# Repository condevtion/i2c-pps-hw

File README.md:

# Schematics for Programmable DC-DC Power Supply with I2C Interface

## About

The repository contains a schematic for the Programmable Power Supply.

## Specifications
- Controller: Texas Instruments [BQ25758S](https://www.ti.com/product/BQ25758S)
- Input voltage: 5V (4-6V - hardware power good window)
- Input current: up to 5A (hardware limited)
- Output voltage: programmable by I2C in controller defined range (3.3 - 26V)
- Output current: up to 5A (hardware limited)
- Switching frequency: 250kHz

## Schematics Structure
The device is complex enough for the schematics to be split into several pages, one for each functional block.
- Controller and Power Stage - consists of the BQ25758S controller, the power MOSFETs, and the inductor
- Input Filter and Sensor - a set of input capacitors and the input current sense resistor connected according to 4-point probes (Kelvin) method
- Output Filter and Sensor - the same for output circuit
- Master Switch - an input protection and an electronically controllable power switch
- Digital I/O and Indication - digital interface between controller and I2C host, contains as well a status LED, a power good LED, and an independent voltage regulator for the digital circuit
- Programming - a set of resistors to define controller's operating mode and HW limits for voltage and current
For now the pages contain mainly just network and hierarchical labels.

## Major Networks and Busses
- **`+5V_Prot`** - protected positive input voltage. The master switch page contains an input connector and protection circuit (fuse, TVS diode, polarity protection) after which the network starts. It is used as well to power the digital I/O and indication block
- **`VINP`** - positive input voltage after the master switch itself (goes to the input filter)
- **`EN`** - master switch control signal (should be high to turn the switch on and low to turn it OFF)
- **`VINN`** - output of the input filter
- **`VOUT`** - the output voltages bus (contains power stage output and whole device output networks, goes to the output filter)
- **`I2C`** - I2C bus itself (connected to `SCL` and `SDA` pins)
- **`GPIO`** - groups digital I/O lines: interrupt, power good, status, and chip enable
- **`PROG`** - groups the rest of analog input lines which should be connected to the programming block to set operating mode and limits for the controller

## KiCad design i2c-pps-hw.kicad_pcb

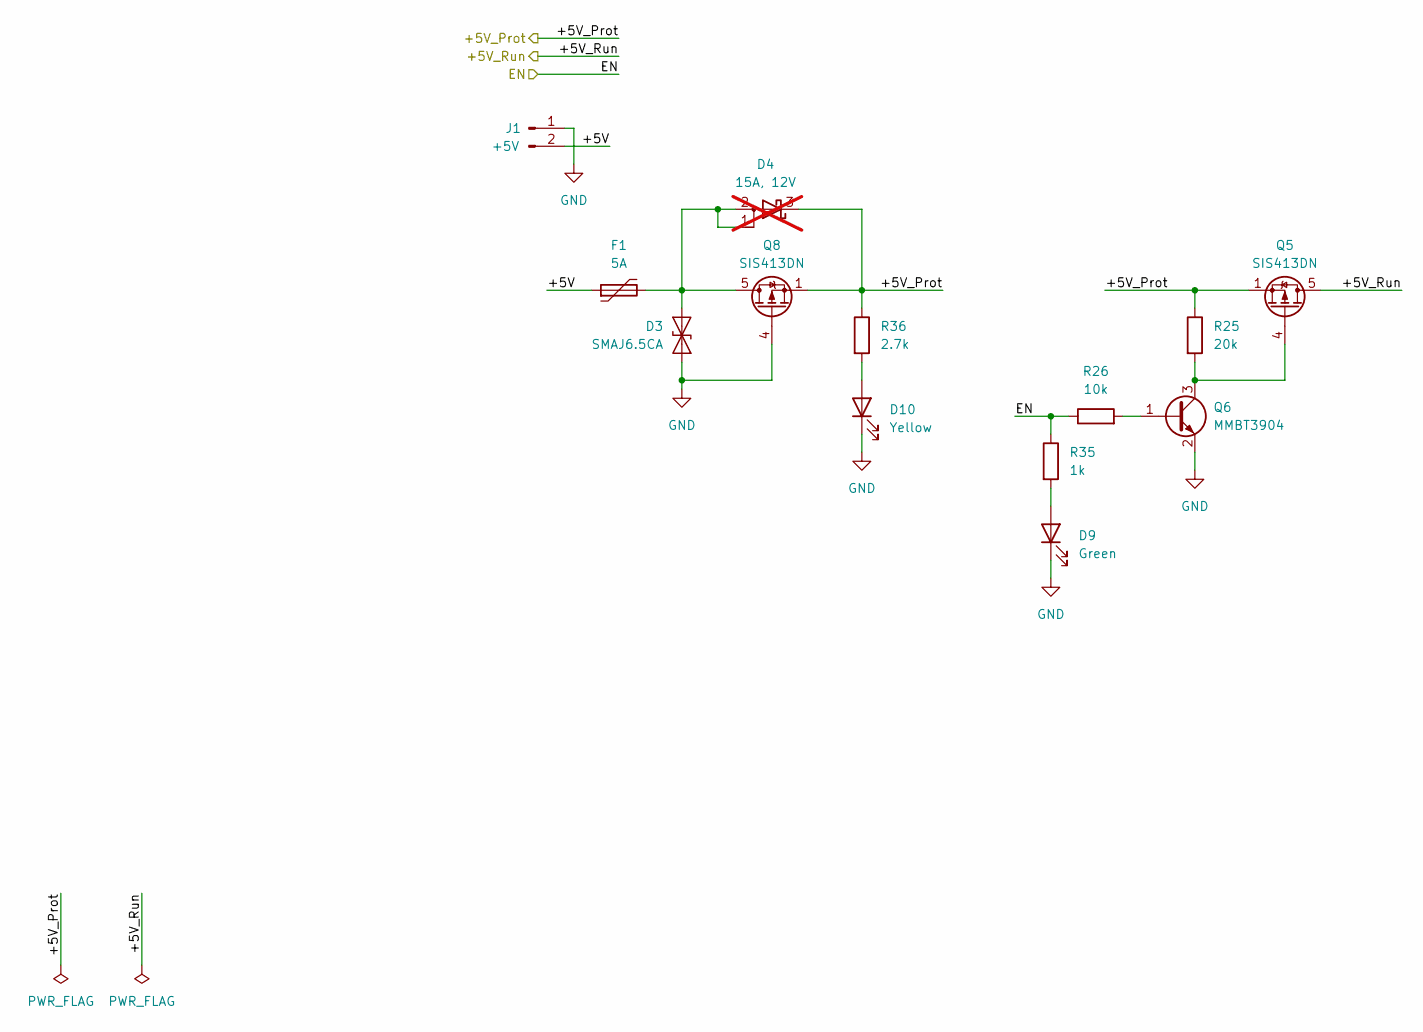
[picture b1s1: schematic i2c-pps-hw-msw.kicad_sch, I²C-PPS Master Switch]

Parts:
D3: SMAJ6.5CA; D_SMA; Part Number SMAJ6.5CA-AT/TR13
D4: 15A, 12V; TO-277A_ThermalVias; Part Number FSV15100V; not fitted
D9: Green; LED_0603_1608Metric_Pad1.05x0.95mm_HandSolder; Part Number LTST-C190GKT
D10: Yellow; LED_0603_1608Metric_Pad1.05x0.95mm_HandSolder; Part Number LTST-C190YKT
F1: 5A; Fuse_2920_7451Metric; Part Number SMD2920B500TF
J1: +5V; TE_1-1123724-2; Part Number 1-1123724-2
Q5, Q8: SIS413DN; Vishay_PowerPAK_1212-8_Single_ThermalVias; Part Number SIS413DN-T1-GE3
Q6: MMBT3904; SOT-23; Part Number MMBT3904-TP
R25: 20k; R_0603_1608Metric_Pad0.98x0.95mm_HandSolder; Part Number RC0603JR-0720KL
R26: 10k; R_0603_1608Metric_Pad0.98x0.95mm_HandSolder; Part Number RC0603JR-0710KL
R35: 1k; R_0603_1608Metric_Pad0.98x0.95mm_HandSolder; Part Number RC0603JR-071KL
R36: 2.7k; R_0603_1608Metric_Pad0.98x0.95mm_HandSolder; Part Number RC0603JR-072K7L

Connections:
/Controller and Power Stage/+5V_Run: Q5.5 (D); also elsewhere on the board
/Digital IO and Indication/+5V_Prot: D4.3 (K), Q5.1 (S), Q5.2 (S), Q5.3 (S), Q8.1 (S), Q8.2 (S), Q8.3 (S), R25.1, R36.1; also elsewhere on the board
/Digital IO and Indication/EN: R26.1, R35.1; also elsewhere on the board
/Master Switch/+5V: F1.1, J1.2
GND: D3.1 (A1), D9.1 (K), D10.1 (K), J1.1, Q6.2 (E), Q8.4 (G); also elsewhere on the board
unnamed: D3.2 (A2), D4.1 (A), D4.2 (A), F1.2, Q8.5 (D)
unnamed: D9.2 (A), R35.2
unnamed: D10.2 (A), R36.2
unnamed: Q5.4 (G), Q6.3 (C), R25.2
unnamed: Q6.1 (B), R26.2

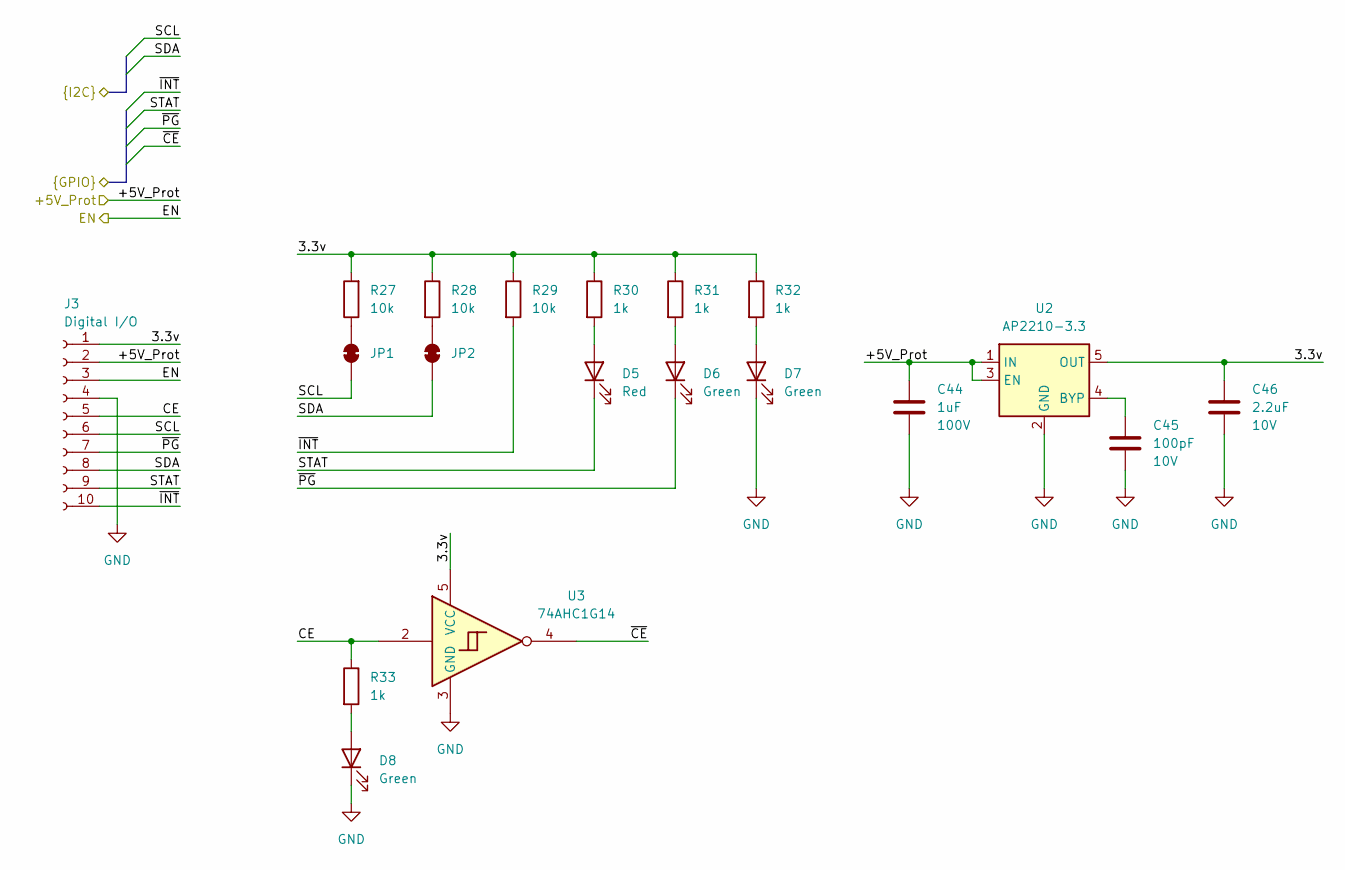
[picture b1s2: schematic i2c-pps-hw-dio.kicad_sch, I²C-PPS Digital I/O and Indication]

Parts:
C44: 1uF; C_0805_2012Metric; Rated Voltage 100V; Part Number 08051C105K4Z2A
C45: 100pF; C_0603_1608Metric_Pad1.08x0.95mm_HandSolder; Rated Voltage 10V; Part Number 885012206003
C46: 2.2uF; C_0603_1608Metric_Pad1.08x0.95mm_HandSolder; Rated Voltage 10V; Part Number GRM188R71A225KE15J
D5: Red; LED_0603_1608Metric_Pad1.05x0.95mm_HandSolder; Part Number LTST-C193KRKT-2A
D6, D7, D8: Green; LED_0603_1608Metric_Pad1.05x0.95mm_HandSolder; Part Number LTST-C190GKT
J3: Digital I/O; PinSocket_2x05_P2.54mm_Vertical; Part Number PPPC052LFBN-RC
JP1, JP2: SolderJumper-2_P0.65mm_Bridged_RoundedPad0.5x0.75mm
R27, R28, R29: 10k; R_0603_1608Metric_Pad0.98x0.95mm_HandSolder; Part Number RC0603JR-0710KL
R30, R31, R32, R33: 1k; R_0603_1608Metric_Pad0.98x0.95mm_HandSolder; Part Number RC0603JR-071KL
U2: AP2210-3.3; SOT-23-5; Part Number AP2210N-3.3TRG1
U3: 74AHC1G14; SOT-23-5_HandSoldering; Part Number SN74AHC1G14DBVR

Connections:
/Controller and Power Stage/SCL: J3.6, JP1.1 (A); also elsewhere on the board
/Controller and Power Stage/SDA: J3.8, JP2.1 (A); also elsewhere on the board
/Controller and Power Stage/STAT: D5.1 (K), J3.9; also elsewhere on the board
/Controller and Power Stage/~CE: U3.4; also elsewhere on the board
/Controller and Power Stage/~INT: J3.10, R29.2; also elsewhere on the board
/Controller and Power Stage/~PG: D6.1 (K), J3.7; also elsewhere on the board
/Digital IO and Indication/3.3v: C46.1, J3.1, R27.2, R28.1, R29.1, R30.1, R31.1, R32.1, U2.5 (OUT), U3.5 (VCC)
/Digital IO and Indication/+5V_Prot: C44.1, J3.2, U2.1 (IN), U2.3 (EN); also elsewhere on the board
/Digital IO and Indication/CE: J3.5, R33.1, U3.2
/Digital IO and Indication/EN: J3.3; also elsewhere on the board
GND: C44.2, C45.2, C46.2, D7.1 (K), D8.1 (K), J3.4, U2.2 (GND), U3.3 (GND); also elsewhere on the board
unnamed: D5.2 (A), R30.2
unnamed: D6.2 (A), R31.2
unnamed: D7.2 (A), R32.2
unnamed: D8.2 (A), R33.2
unnamed: JP1.2 (B), R27.1
unnamed: JP2.2 (B), R28.2
unnamed: C45.1, U2.4 (BYP)

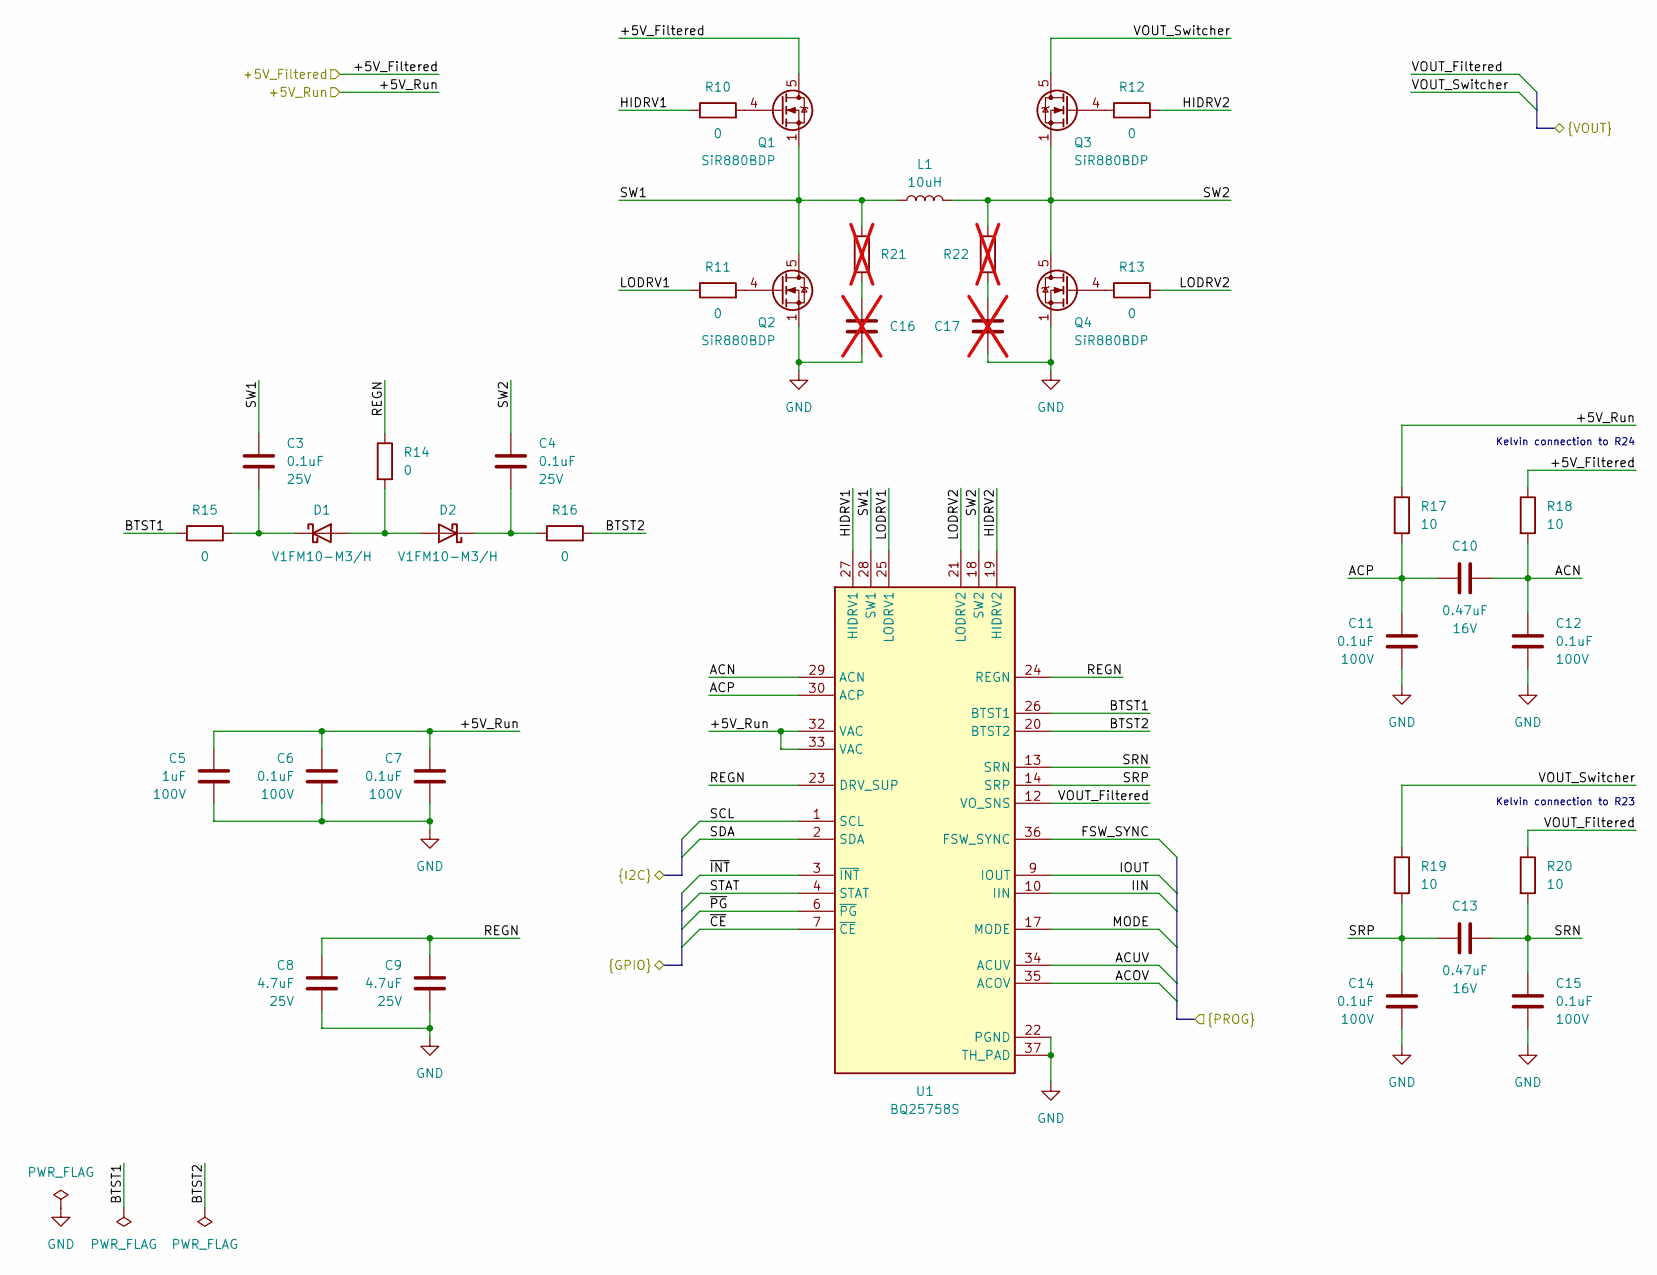
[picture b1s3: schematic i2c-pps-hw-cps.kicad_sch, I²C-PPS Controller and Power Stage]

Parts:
C3, C4: 0.1uF; C_0603_1608Metric_Pad1.08x0.95mm_HandSolder; Rated Voltage 25V; Part Number C0603C104K3RACTU
C5: 1uF; C_0805_2012Metric; Rated Voltage 100V; Part Number 08051C105K4Z2A
C6, C7, C11, C12, C14, C15: 0.1uF; C_0603_1608Metric_Pad1.08x0.95mm_HandSolder; Rated Voltage 100V; Part Number HMK107B7104KAHT
C8, C9: 4.7uF; C_0805_2012Metric; Rated Voltage 25V; Part Number CGA4J1X7R1E475K125AE
C10, C13: 0.47uF; C_0603_1608Metric_Pad1.08x0.95mm_HandSolder; Rated Voltage 16V; Part Number CL10B474KO8NNNC
C16, C17: C_0805_2012Metric; not fitted
D1, D2: V1FM10-M3/H; D_SMF; Part Number V1FM10-M3/H
L1: 10uH; L_Bourns_SRP1038A_10.0x11.0mm; Part Number SRP1038A-100M
Q1, Q2, Q3, Q4: SiR880BDP; PowerPAK_SO-8_Single_ThermalVias; Part Number SIR880BDP-T1-RE3
R10, R11, R12, R13, R15, R16: 0; R_0603_1608Metric_Pad0.98x0.95mm_HandSolder; Part Number RC0603JR-070RL
R14: 0; R_0805_2012Metric; Part Number CRCW08050000Z0EAC
R17, R18, R19, R20: 10; R_0603_1608Metric_Pad0.98x0.95mm_HandSolder; Part Number RC0603FR-0710RL
R21, R22: R_1210_3225Metric; not fitted
U1: BQ25758S; Texas_RRV0036A_VQFN-36-1EP_4.8x5.8mm_P0.5mm_EP3.6x4.6mm_The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; Part Number BQ25758SRRVR

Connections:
/Controller and Power Stage/+5V_Filtered: Q1.5 (D), R18.1; also elsewhere on the board
/Controller and Power Stage/+5V_Run: C5.1, C6.1, C7.1, R17.1, U1.32 (VAC), U1.33 (VAC); also elsewhere on the board
/Controller and Power Stage/ACN: C10.1, C12.1, R18.2, U1.29 (ACN)
/Controller and Power Stage/ACOV: U1.35 (ACOV); also elsewhere on the board
/Controller and Power Stage/ACP: C10.2, C11.1, R17.2, U1.30 (ACP)
/Controller and Power Stage/ACUV: U1.34 (ACUV); also elsewhere on the board
/Controller and Power Stage/BTST1: R15.1, U1.26 (BTST1)
/Controller and Power Stage/BTST2: R16.2, U1.20 (BTST2)
/Controller and Power Stage/FSW_SYNC: U1.36 (FSW_SYNC); also elsewhere on the board
/Controller and Power Stage/HIDRV1: R10.1, U1.27 (HIDRV1)
/Controller and Power Stage/HIDRV2: R12.2, U1.19 (HIDRV2)
/Controller and Power Stage/IIN: U1.10 (IIN); also elsewhere on the board
/Controller and Power Stage/IOUT: U1.9 (IOUT); also elsewhere on the board
/Controller and Power Stage/LODRV1: R11.1, U1.25 (LODRV1)
/Controller and Power Stage/LODRV2: R13.2, U1.21 (LODRV2)
/Controller and Power Stage/MODE: U1.17 (MODE); also elsewhere on the board
/Controller and Power Stage/REGN: C8.1, C9.1, R14.1, U1.23 (DRV_SUP), U1.24 (REGN)
/Controller and Power Stage/SCL: U1.1 (SCL); also elsewhere on the board
/Controller and Power Stage/SDA: U1.2 (SDA); also elsewhere on the board
/Controller and Power Stage/SRN: C13.1, C15.1, R20.2, U1.13 (SRN)
/Controller and Power Stage/SRP: C13.2, C14.1, R19.2, U1.14 (SRP)
/Controller and Power Stage/STAT: U1.4 (STAT); also elsewhere on the board
/Controller and Power Stage/SW1: C3.1, L1.1, Q1.1 (S), Q1.2 (S), Q1.3 (S), Q2.5 (D), R21.1, U1.28 (SW1)
/Controller and Power Stage/SW2: C4.1, L1.2, Q3.1 (S), Q3.2 (S), Q3.3 (S), Q4.5 (D), R22.1, U1.18 (SW2)
/Controller and Power Stage/VOUT_Filtered: R20.1, U1.12 (VO_SNS); also elsewhere on the board
/Controller and Power Stage/VOUT_Switcher: Q3.5 (D), R19.1; also elsewhere on the board
/Controller and Power Stage/~CE: U1.7 (~CE); also elsewhere on the board
/Controller and Power Stage/~INT: U1.3 (~INT); also elsewhere on the board
/Controller and Power Stage/~PG: U1.6 (~PG); also elsewhere on the board
GND: C5.2, C6.2, C7.2, C8.2, C9.2, C11.2, C12.2, C14.2, C15.2, C16.2, C17.2, Q2.1 (S), Q2.2 (S), Q2.3 (S), Q4.1 (S), Q4.2 (S), Q4.3 (S), U1.22 (PGND), U1.37 (TH_PAD); also elsewhere on the board
unnamed: C16.1, R21.2
unnamed: C17.1, R22.2
unnamed: D1.2 (A), D2.2 (A), R14.2
unnamed: C3.2, D1.1 (K), R15.2
unnamed: C4.2, D2.1 (K), R16.1
unnamed: Q1.4 (G), R10.2
unnamed: Q2.4 (G), R11.2
unnamed: Q3.4 (G), R12.1
unnamed: Q4.4 (G), R13.1

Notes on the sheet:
Kelvin connection to R24
Kelvin connection to R23

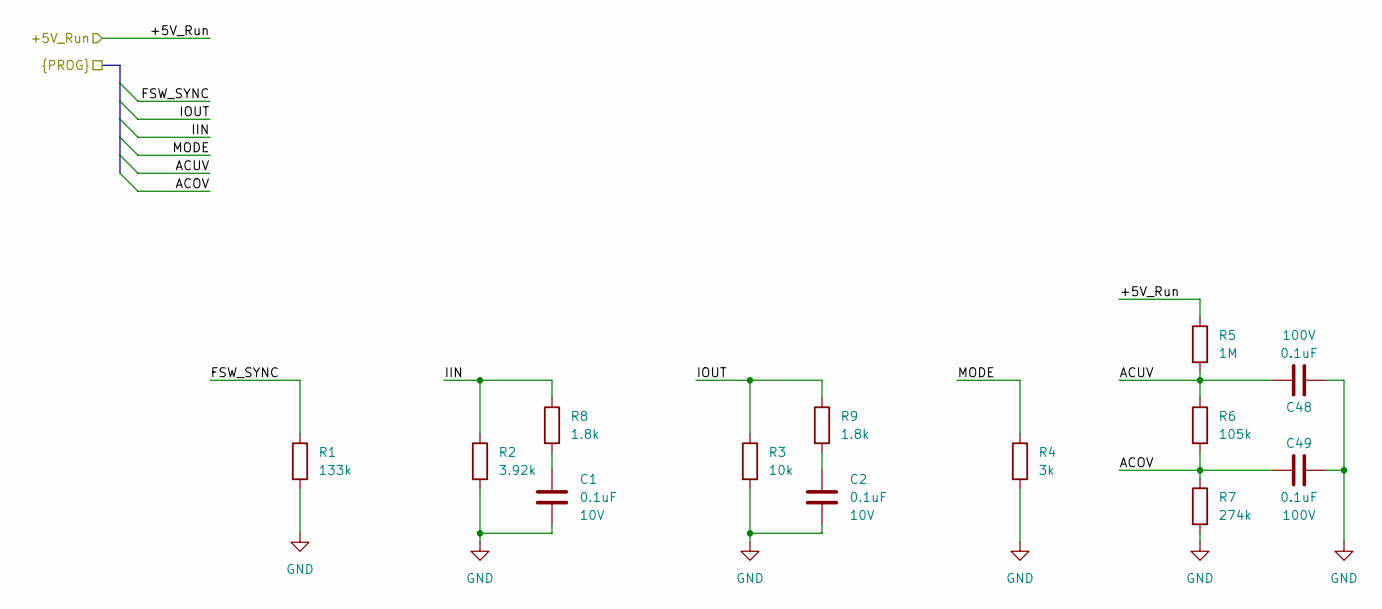
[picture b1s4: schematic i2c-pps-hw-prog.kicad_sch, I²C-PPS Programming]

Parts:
C1, C2: 0.1uF; C_0603_1608Metric_Pad1.08x0.95mm_HandSolder; Rated Voltage 10V; Part Number C0603C104K8RACTU
C48, C49: 0.1uF; C_0603_1608Metric_Pad1.08x0.95mm_HandSolder; Rated Voltage 100V; Part Number HMK107B7104KAHT
R1: 133k; R_0603_1608Metric_Pad0.98x0.95mm_HandSolder; Part Number RC0603FR-07133KL
R2: 3.92k; R_0603_1608Metric_Pad0.98x0.95mm_HandSolder; Part Number RC0603FR-073K92L
R3: 10k; R_0603_1608Metric_Pad0.98x0.95mm_HandSolder; Part Number RC0603FR-0710KL
R4: 3k; R_0603_1608Metric_Pad0.98x0.95mm_HandSolder; Part Number RC0603FR-073KL
R5: 1M; R_0805_2012Metric; Part Number ERA-6AEB105V
R6: 105k; R_0805_2012Metric; Part Number ERA-6AEB1053V
R7: 274k; R_0805_2012Metric; Part Number ERA-6AEB2743V
R8, R9: 1.8k; R_0603_1608Metric_Pad0.98x0.95mm_HandSolder; Part Number RC0603JR-071K8L

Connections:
/Controller and Power Stage/+5V_Run: R5.1; also elsewhere on the board
/Controller and Power Stage/ACOV: C49.1, R6.2, R7.1; also elsewhere on the board
/Controller and Power Stage/ACUV: C48.1, R5.2, R6.1; also elsewhere on the board
/Controller and Power Stage/FSW_SYNC: R1.1; also elsewhere on the board
/Controller and Power Stage/IIN: R2.1, R8.1; also elsewhere on the board
/Controller and Power Stage/IOUT: R3.1, R9.1; also elsewhere on the board
/Controller and Power Stage/MODE: R4.1; also elsewhere on the board
GND: C1.2, C2.2, C48.2, C49.2, R1.2, R2.2, R3.2, R4.2, R7.2; also elsewhere on the board
unnamed: C1.1, R8.2
unnamed: C2.1, R9.2

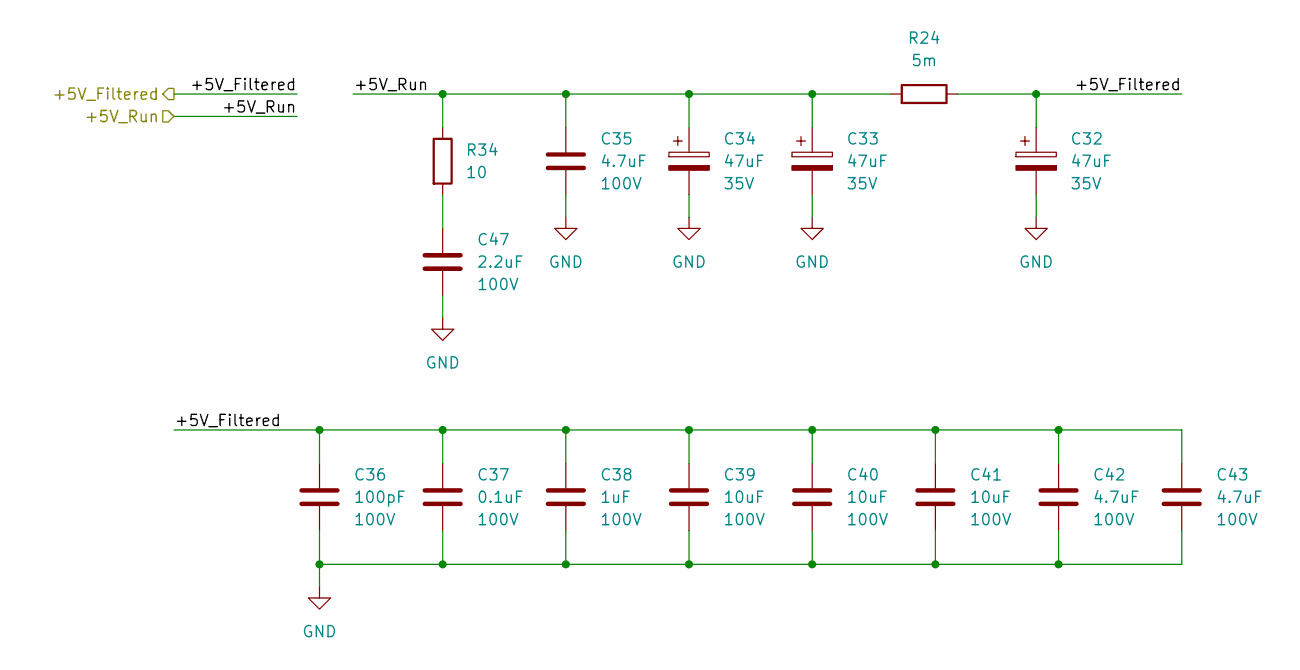
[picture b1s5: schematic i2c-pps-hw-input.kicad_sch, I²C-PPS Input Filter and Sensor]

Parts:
C32, C33, C34: 47uF; CP_Elec_6.3x5.7; Rated Voltage 35V; Part Number A768EB476M1VLAE042
C35, C42, C43: 4.7uF; C_1210_3225Metric; Rated Voltage 100V; Part Number GCJ32DC72A475KE01L
C36: 100pF; C_0603_1608Metric_Pad1.08x0.95mm_HandSolder; Rated Voltage 100V; Part Number CGA3E2C0G2A101J080AA
C37: 0.1uF; C_0603_1608Metric_Pad1.08x0.95mm_HandSolder; Rated Voltage 100V; Part Number HMK107B7104KAHT
C38: 1uF; C_0805_2012Metric; Rated Voltage 100V; Part Number 08051C105K4Z2A
C39, C40, C41: 10uF; C_1210_3225Metric; Rated Voltage 100V; Part Number C3225X7R2A106K250AC
C47: 2.2uF; C_1210_3225Metric; Rated Voltage 100V; Part Number CGA6N3X7R2A225K230AE
R24: 5m; R_2512_6332Metric; Part Number PA2512FKM070R005E
R34: 10; R_1206_3216Metric; Part Number SR1206FR-7T10RL

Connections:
/Controller and Power Stage/+5V_Filtered: C32.1, C36.1, C37.1, C38.1, C39.1, C40.1, C41.1, C42.1, C43.1, R24.1; also elsewhere on the board
/Controller and Power Stage/+5V_Run: C33.1, C34.1, C35.1, R24.2, R34.1; also elsewhere on the board
GND: C32.2, C33.2, C34.2, C35.2, C36.2, C37.2, C38.2, C39.2, C40.2, C41.2, C42.2, C43.2, C47.2; also elsewhere on the board
unnamed: C47.1, R34.2

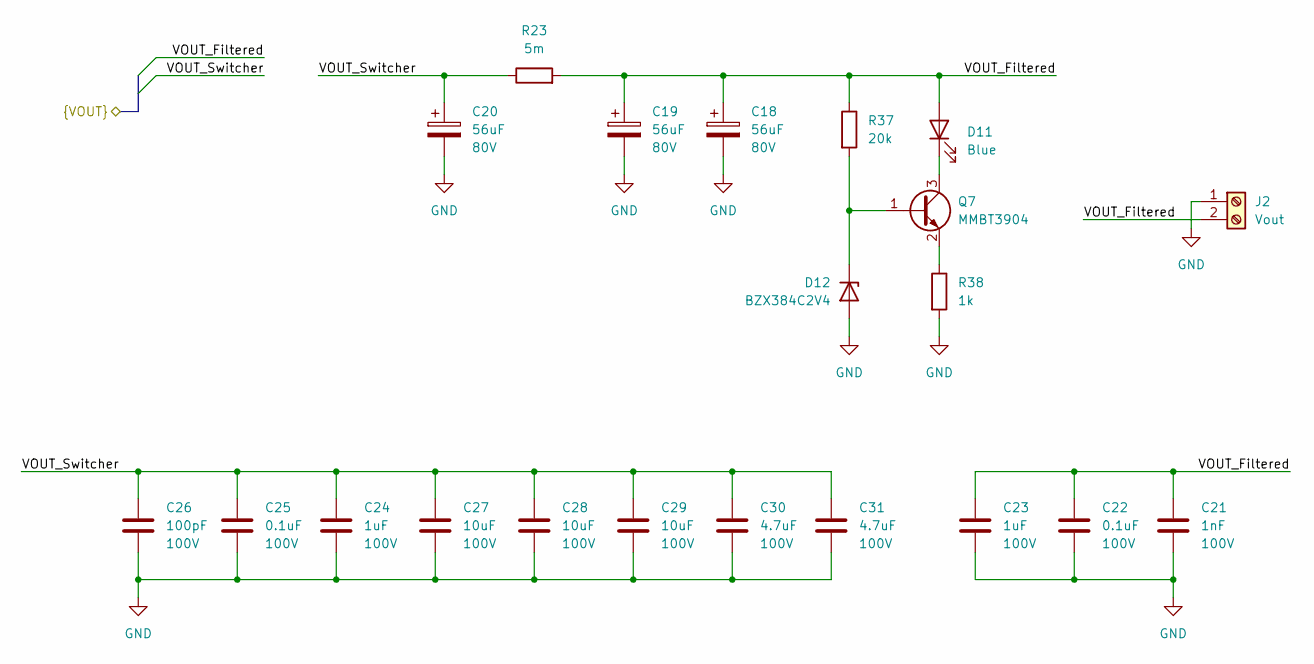
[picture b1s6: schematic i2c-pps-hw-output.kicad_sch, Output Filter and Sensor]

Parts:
C18, C19, C20: 56uF; C_Elec_10x10.2; Rated Voltage 80V; Part Number A768MS566M1KLAE034
C21: 1nF; C_0603_1608Metric_Pad1.08x0.95mm_HandSolder; Rated Voltage 100V; Part Number CGA3E2X7R2A102K080AA
C22, C25: 0.1uF; C_0603_1608Metric_Pad1.08x0.95mm_HandSolder; Rated Voltage 100V; Part Number HMK107B7104KAHT
C23, C24: 1uF; C_0805_2012Metric; Rated Voltage 100V; Part Number 08051C105K4Z2A
C26: 100pF; C_0603_1608Metric_Pad1.08x0.95mm_HandSolder; Rated Voltage 100V; Part Number CGA3E2C0G2A101J080AA
C27, C28, C29: 10uF; C_1210_3225Metric; Rated Voltage 100V; Part Number C3225X7R2A106K250AC
C30, C31: 4.7uF; C_1210_3225Metric; Rated Voltage 100V; Part Number GCJ32DC72A475KE01L
D11: Blue; LED_0603_1608Metric_Pad1.05x0.95mm_HandSolder; Part Number LTST-C193TBKT-5A
D12: BZX384C2V4; D_SOD-323; Part Number BZX384C2V4-E3-08
J2: Vout; TerminalBlock_MetzConnect_Type101_RT01602HBWC_1x02_P5.08mm_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; Part Number TB006-508-02BE
Q7: MMBT3904; SOT-23; Part Number MMBT3904-TP
R23: 5m; R_2512_6332Metric; Part Number PA2512FKM070R005E
R37: 20k; R_0603_1608Metric_Pad0.98x0.95mm_HandSolder; Part Number RC0603JR-0720KL
R38: 1k; R_0603_1608Metric_Pad0.98x0.95mm_HandSolder; Part Number RC0603JR-071KL

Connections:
/Controller and Power Stage/VOUT_Filtered: C18.1, C19.1, C21.1, C22.1, C23.1, D11.2 (A), J2.2, R23.2, R37.1; also elsewhere on the board
/Controller and Power Stage/VOUT_Switcher: C20.1, C24.1, C25.1, C26.1, C27.1, C28.1, C29.1, C30.1, C31.1, R23.1; also elsewhere on the board
GND: C18.2, C19.2, C20.2, C21.2, C22.2, C23.2, C24.2, C25.2, C26.2, C27.2, C28.2, C29.2, C30.2, C31.2, D12.2 (A), J2.1, R38.2; also elsewhere on the board
unnamed: D11.1 (K), Q7.3 (C)
unnamed: D12.1 (K), Q7.1 (B), R37.2
unnamed: Q7.2 (E), R38.1

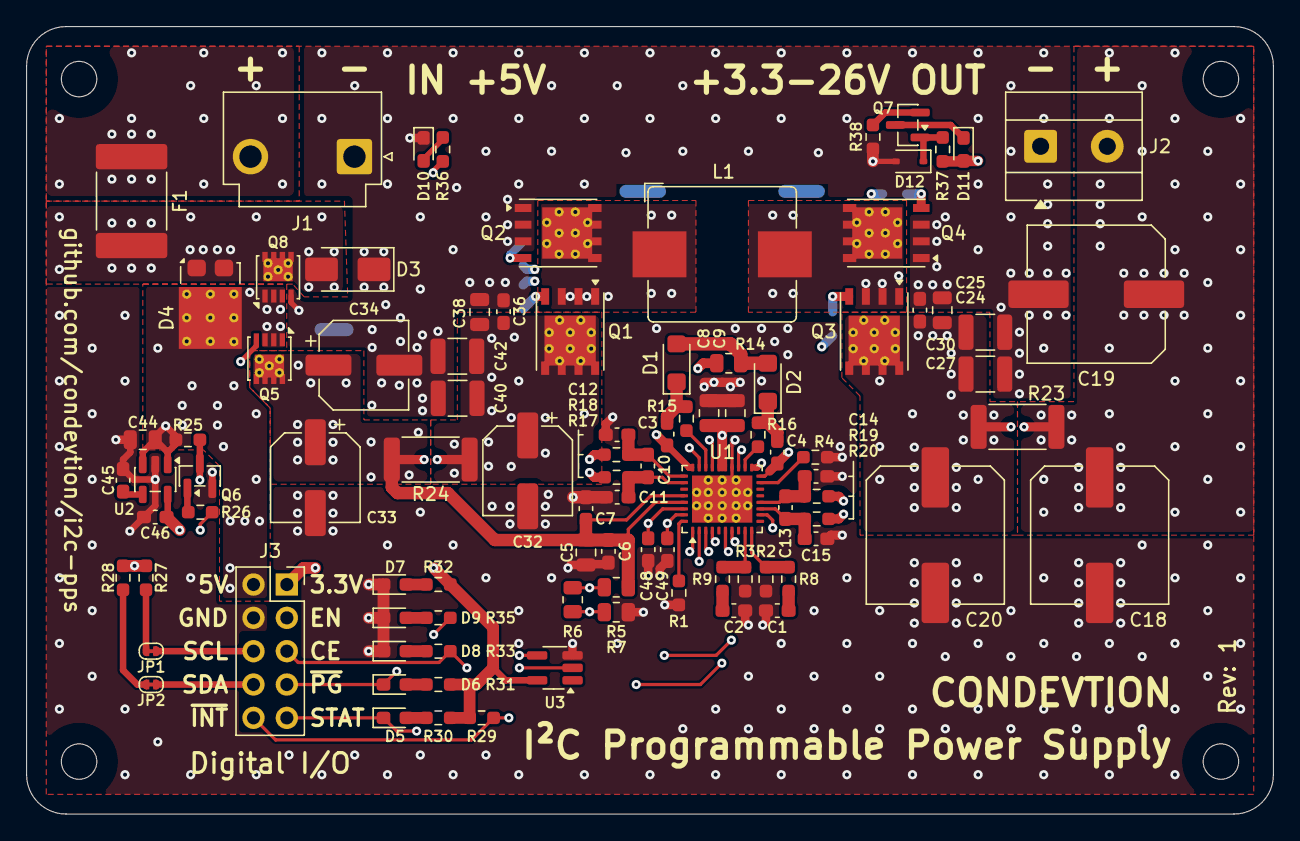
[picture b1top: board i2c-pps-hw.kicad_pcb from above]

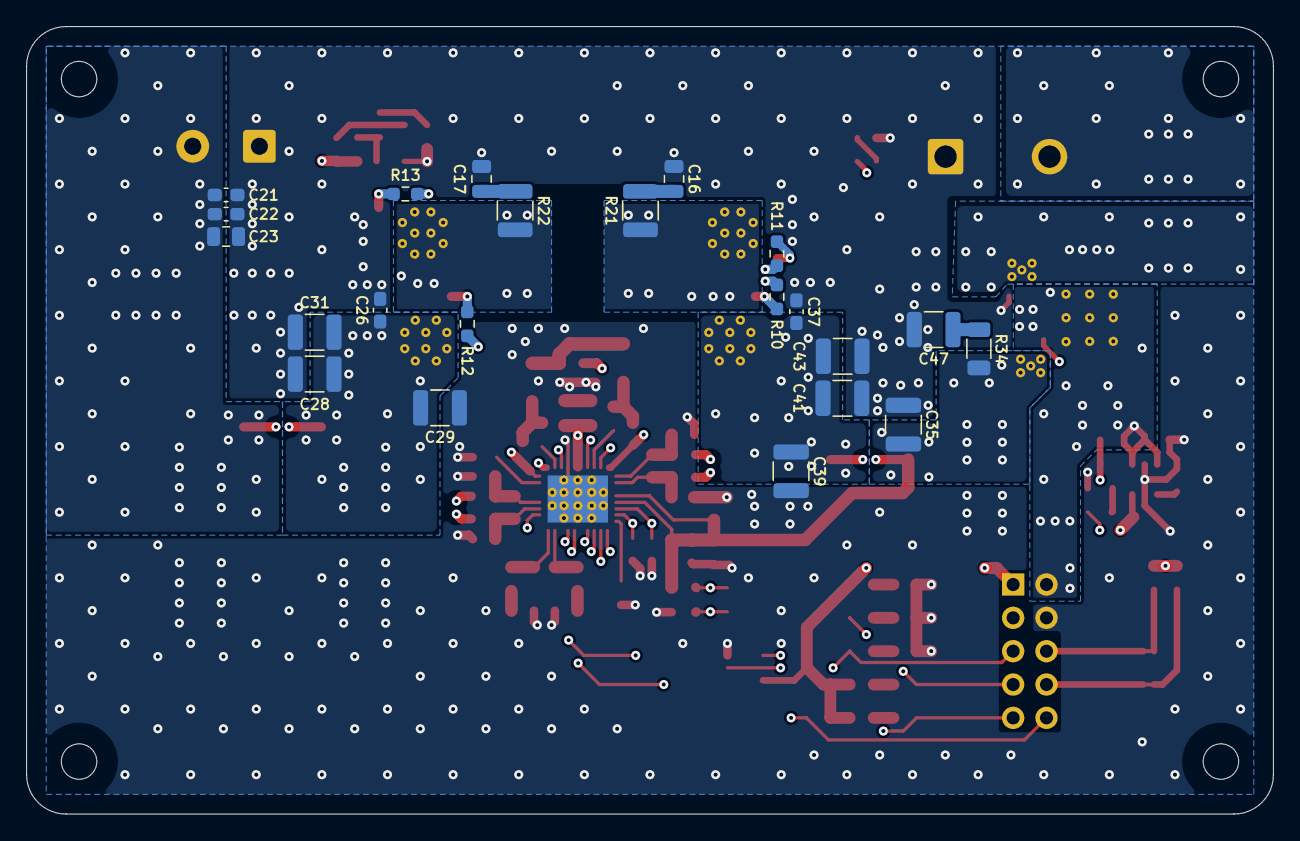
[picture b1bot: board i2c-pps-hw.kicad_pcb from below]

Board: 4 copper layers, 95.0 x 60.0 mm, 121 parts (22 on the bottom side), 62 nets.

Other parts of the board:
MH1, MH2, MH3, MH4: MountingHole_2.7mm_M2.5_Guarded

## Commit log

2026-02-19 Create initial version of the schematics
2026-02-20 Add symbol and footprints for the BQ25758S controller
2026-02-22 Create a page per devices block and connect them
2026-02-28 Design schematics and set per component requirements
2026-02-28 Remove CSIN and CSOUT busses from readme as they have been deleted from schematics
2026-03-12 Switch to MOSFET based polarity protection
2026-03-12 Rename VOUTP to VOUT_Switcher for clarity
2026-03-12 Add more indicator LEDs
2026-03-12 Rename VINP to +5V_Run for clarity
2026-03-12 Rename VOUTN to VOUT_Filtered for clarity
2026-03-12 Rename VINN to +5V_Filtered for clarity
2026-03-12 Rename VIN to +5V_Prot for clarity
2026-03-12 Remove alias CSIN as the bus has been removed
2026-03-12 Fix errors and warnings reported by ERC
2026-03-12 Select market available components
2026-03-12 Create an empty PCB with RPi5/Z2 dimensions
2026-03-12 Setup the board and move components from schematics
2026-03-13 Add PCBWay custom design rules, adjust board constraints, and physical stackup for 4-layers 2/1.5oz copper
2026-03-15 Adjust design rules and footprints to fit each other
2026-03-15 Route driving part of the power stage
2026-03-17 Place and route controller surroundings
2026-03-19 Place and route power stage
2026-03-19 Add thermal vias to the power stage transistors
2026-03-19 Remove mounting and resize board
2026-03-24 Implement approximate component placement
2026-03-24 Add thermal vias to the master switch components
2026-04-07 Route the PCB
2026-04-07 Add manufacturer and part number to Vout terminal
2026-04-10 Add more vias
2026-04-17 Adjust vias, GND top zone, and setup fabrication output
